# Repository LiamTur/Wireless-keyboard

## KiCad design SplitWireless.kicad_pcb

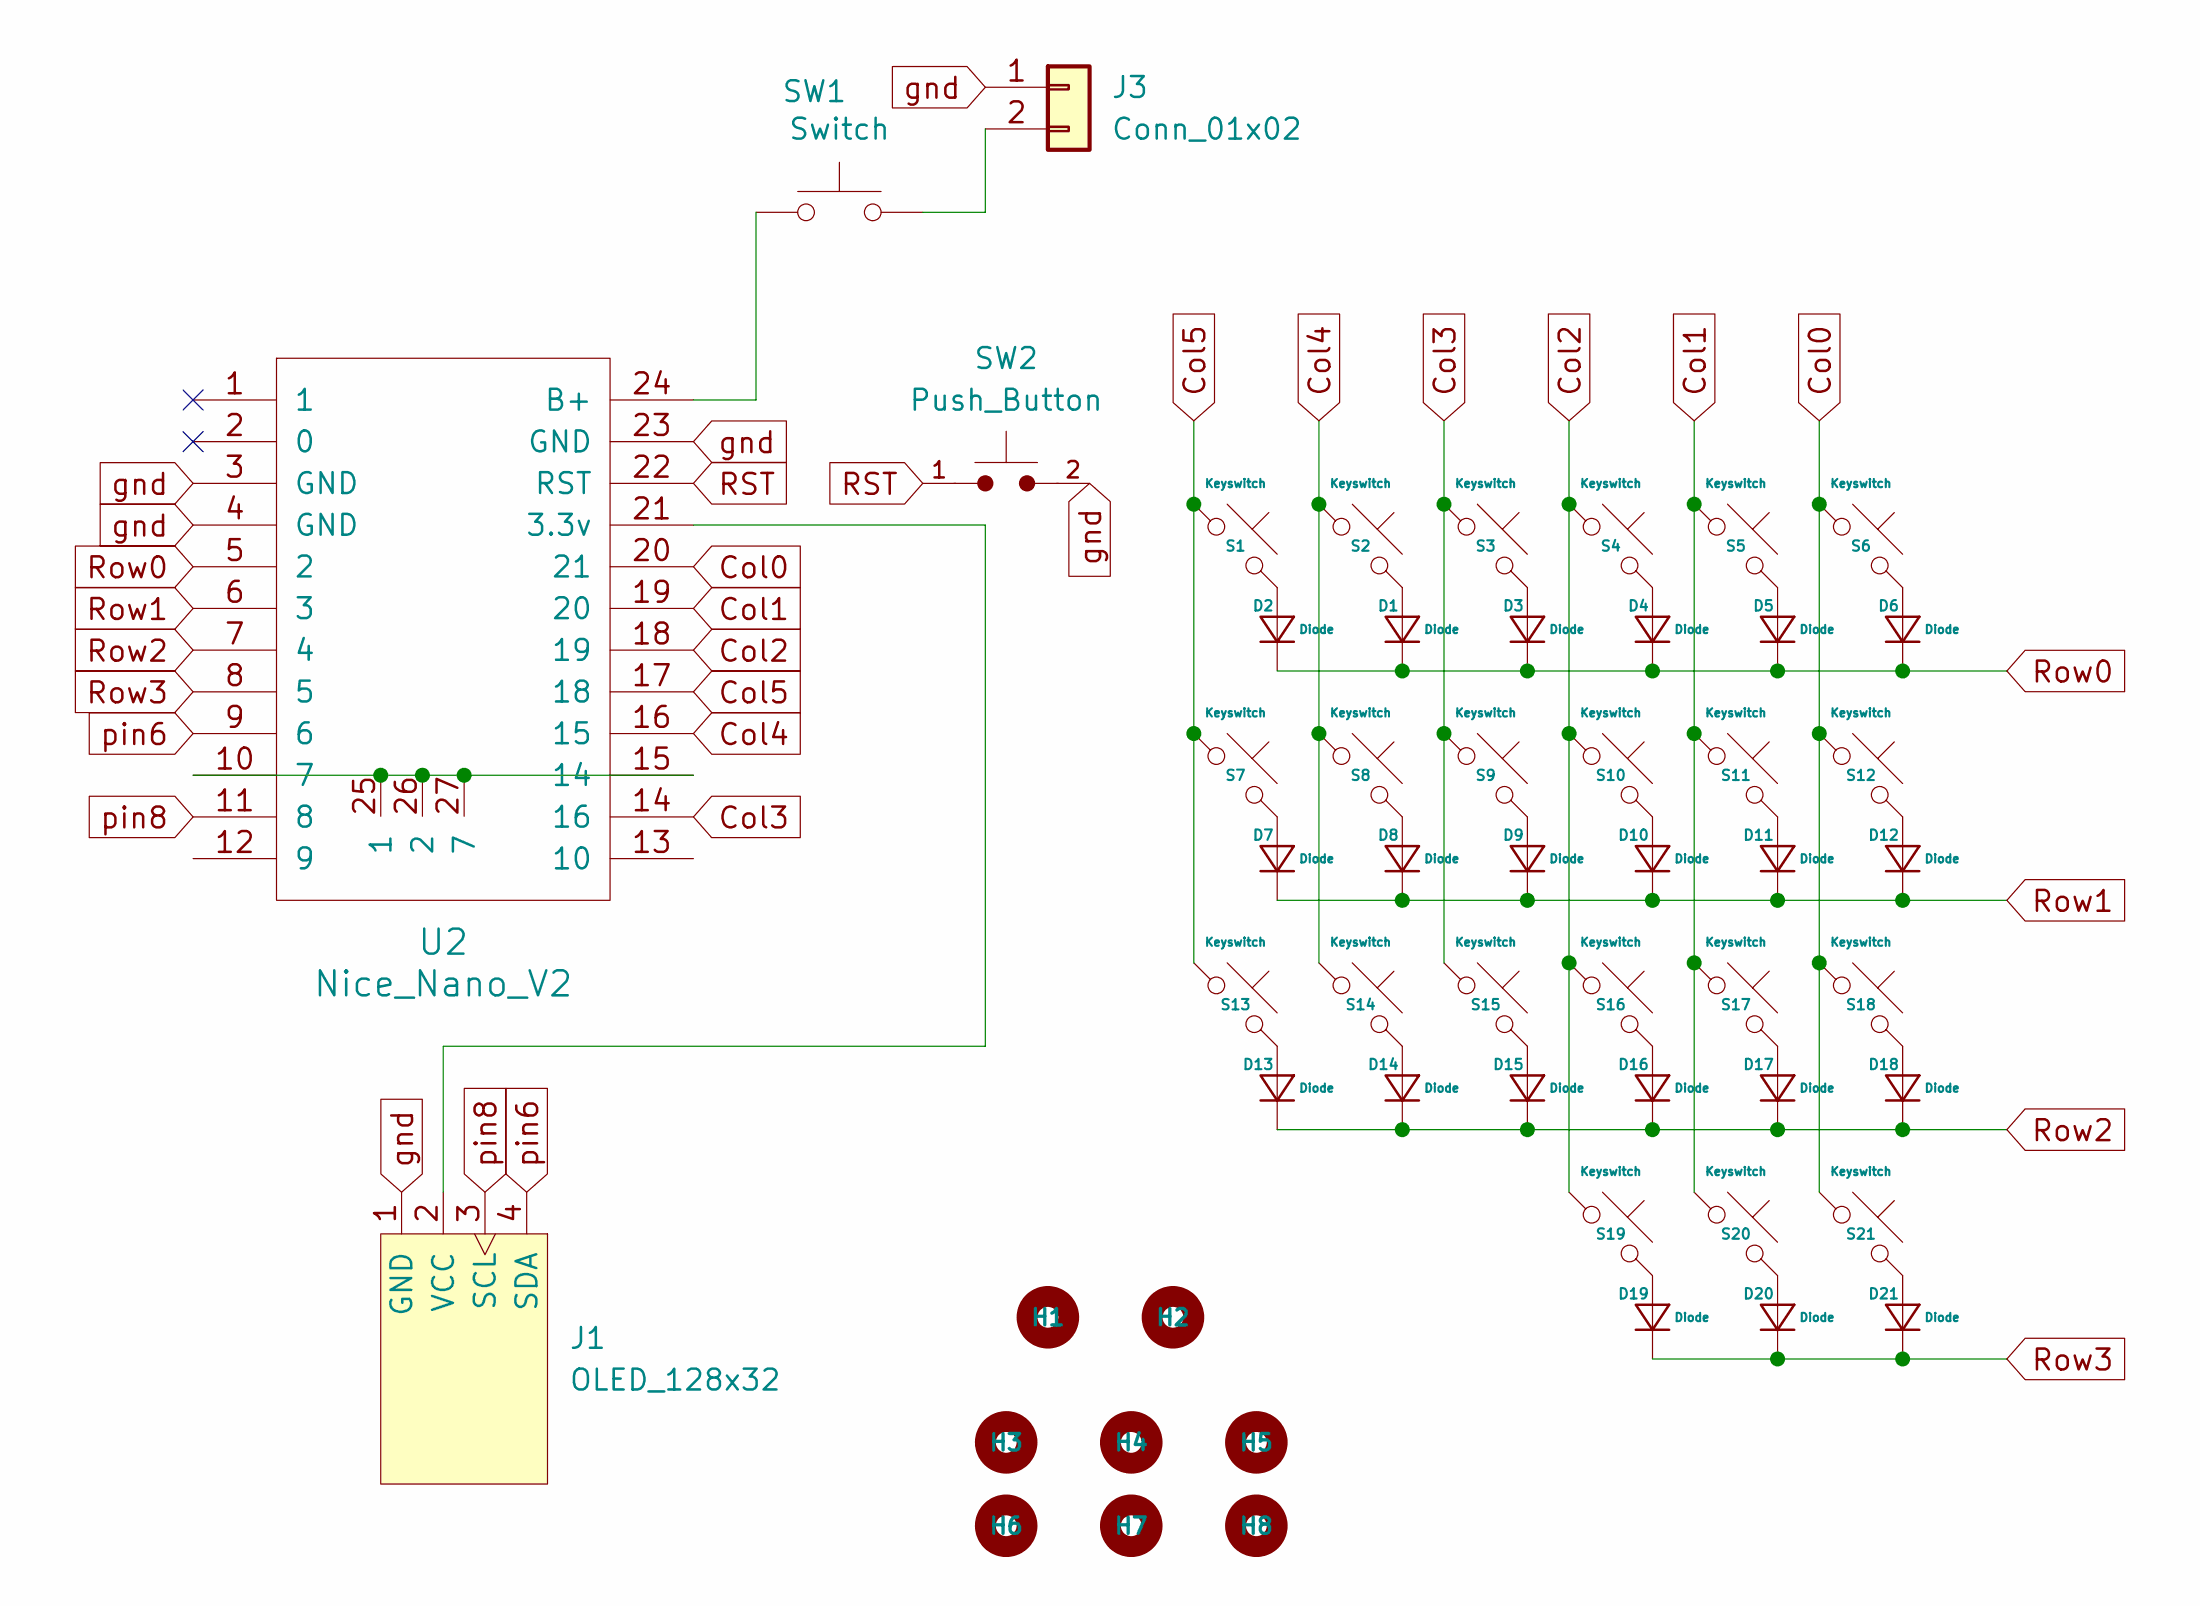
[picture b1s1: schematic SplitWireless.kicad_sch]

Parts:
D1, D2, D3, D4, D5, D6, D7, D8, D9, D10, D11, D12, D13, D14, D15, D16, D17, D18, D19, D20, D21: Diode; Diode_DO-35
H1, H2, H3, H4, H5, H6, H7, H8: MountingHole_2-56
J1: OLED_128x32
J3: Conn_01x02; Connector_1x02_JST-PH; Part Number 1-0201FBV0T
S1, S2, S3, S4, S5, S6, S7, S8, S9, S10, S11, S12, S13, S14, S15, S16, S17, S18, S19, S20, S21: Keyswitch; MX_Hotswap_1.00u
SW1: Switch; SW_SPDT_PCM12
SW2: Push_Button; Panasonic_EVQPUJ_EVQPUA
U2: Nice_Nano_V2

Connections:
Col0: S6.1, S12.1, S18.1, S21.1, U2.20 (21)
Col1: S5.1, S11.1, S17.1, S20.1, U2.19 (20)
Col2: S4.1, S10.1, S16.1, S19.1, U2.18 (19)
Col3: S3.1, S9.1, S15.1, U2.14 (16)
Col4: S2.1, S8.1, S14.1, U2.16 (15)
Col5: S1.1, S7.1, S13.1, U2.17 (18)
unnamed: D1.2 (A), S2.2
unnamed: D2.2 (A), S1.2
unnamed: D3.2 (A), S3.2
unnamed: D4.2 (A), S4.2
unnamed: D5.2 (A), S5.2
unnamed: D6.2 (A), S6.2
unnamed: D7.2 (A), S7.2
unnamed: D8.2 (A), S8.2
unnamed: D9.2 (A), S9.2
unnamed: D10.2 (A), S10.2
unnamed: D11.2 (A), S11.2
unnamed: D12.2 (A), S12.2
unnamed: D13.2 (A), S13.2
unnamed: D14.2 (A), S14.2
unnamed: D15.2 (A), S15.2
unnamed: D16.2 (A), S16.2
unnamed: D17.2 (A), S17.2
unnamed: D18.2 (A), S18.2
unnamed: D19.2 (A), S19.2
unnamed: D20.2 (A), S20.2
unnamed: D21.2 (A), S21.2
unnamed: J1.2 (VCC), U2.21 (3.3v)
unnamed: J3.2, SW1.2
unnamed: U2.10 (7), U2.15 (14), U2.25 (1), U2.26 (2), U2.27 (7)
unnamed: SW1.1, U2.24 (B+)
RST: SW2.1, U2.22 (RST)
Row0: D1.1 (K), D2.1 (K), D3.1 (K), D4.1 (K), D5.1 (K), D6.1 (K), U2.5 (2)
Row1: D7.1 (K), D8.1 (K), D9.1 (K), D10.1 (K), D11.1 (K), D12.1 (K), U2.6 (3)
Row2: D13.1 (K), D14.1 (K), D15.1 (K), D16.1 (K), D17.1 (K), D18.1 (K), U2.7 (4)
Row3: D19.1 (K), D20.1 (K), D21.1 (K), U2.8 (5)
gnd: J1.1 (GND), J3.1, SW2.2, U2.3 (GND), U2.4 (GND), U2.23 (GND)
pin6: J1.4 (SDA), U2.9 (6)
pin8: J1.3 (SCL), U2.11 (8)

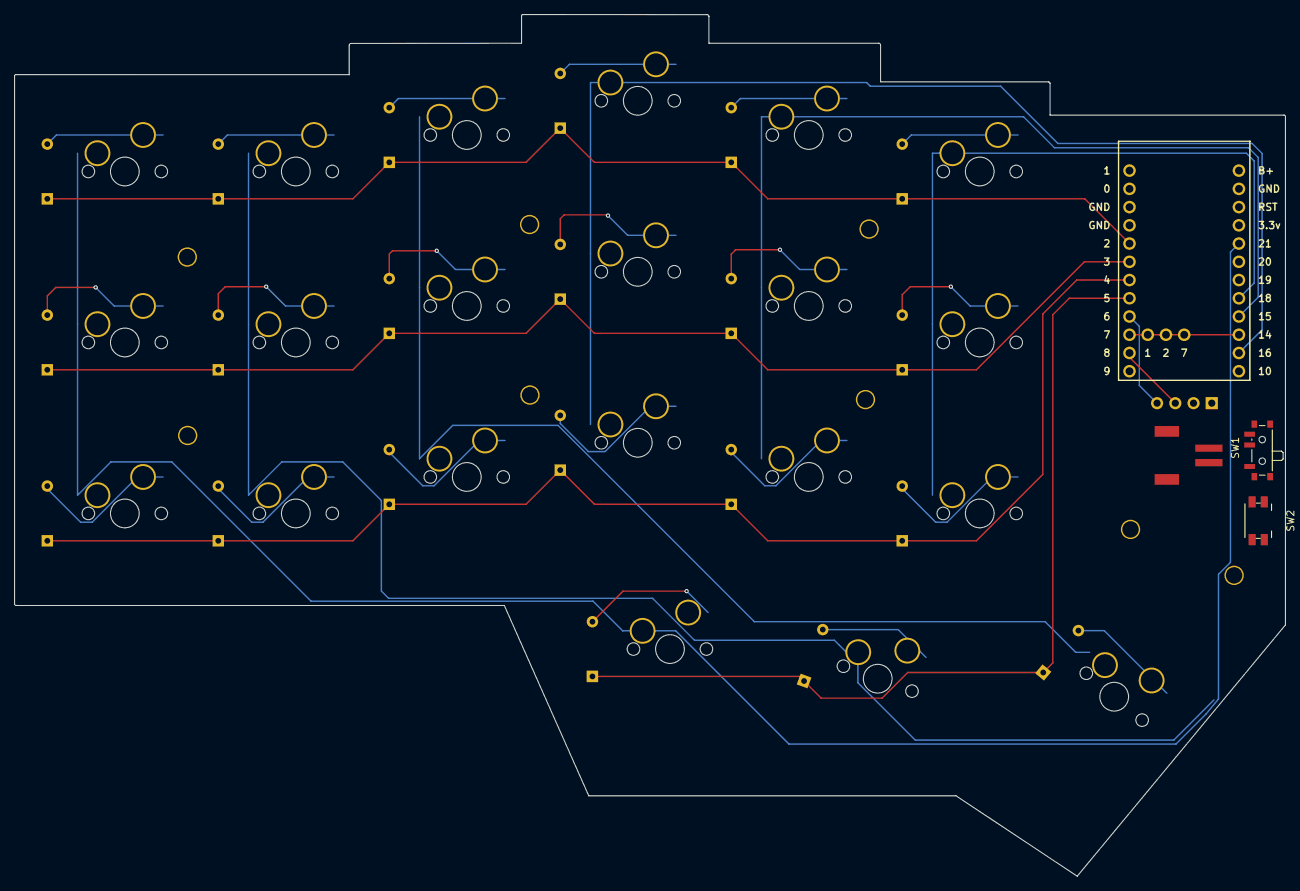
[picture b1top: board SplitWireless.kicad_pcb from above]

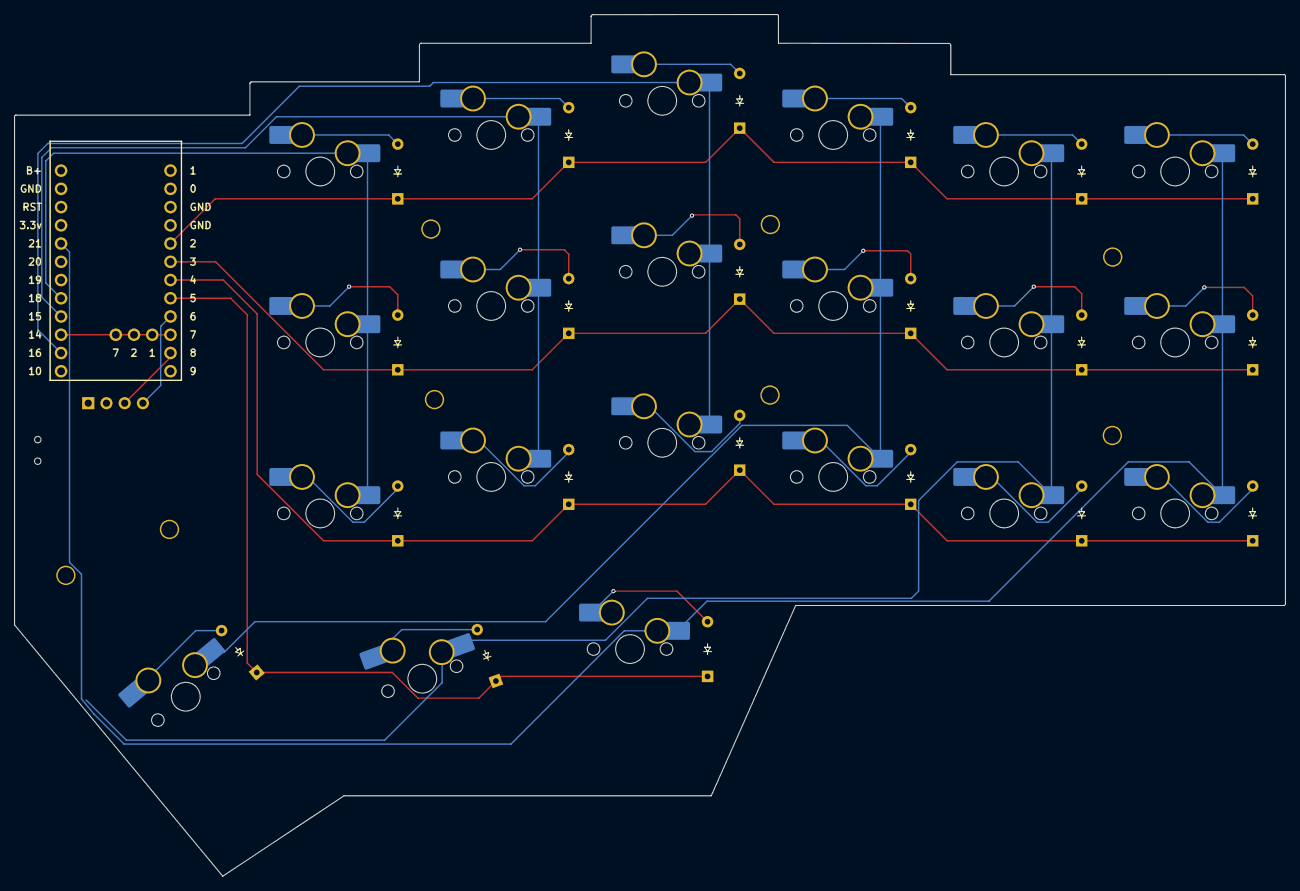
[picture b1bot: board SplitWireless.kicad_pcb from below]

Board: 2 copper layers, 177.0 x 120.0 mm, 55 parts (42 on the bottom side), 39 nets.

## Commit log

2026-03-09 some shitty keyboard
2026-03-12 added some stuff
2026-03-12 removed choc and some shit
2026-03-19 workin
